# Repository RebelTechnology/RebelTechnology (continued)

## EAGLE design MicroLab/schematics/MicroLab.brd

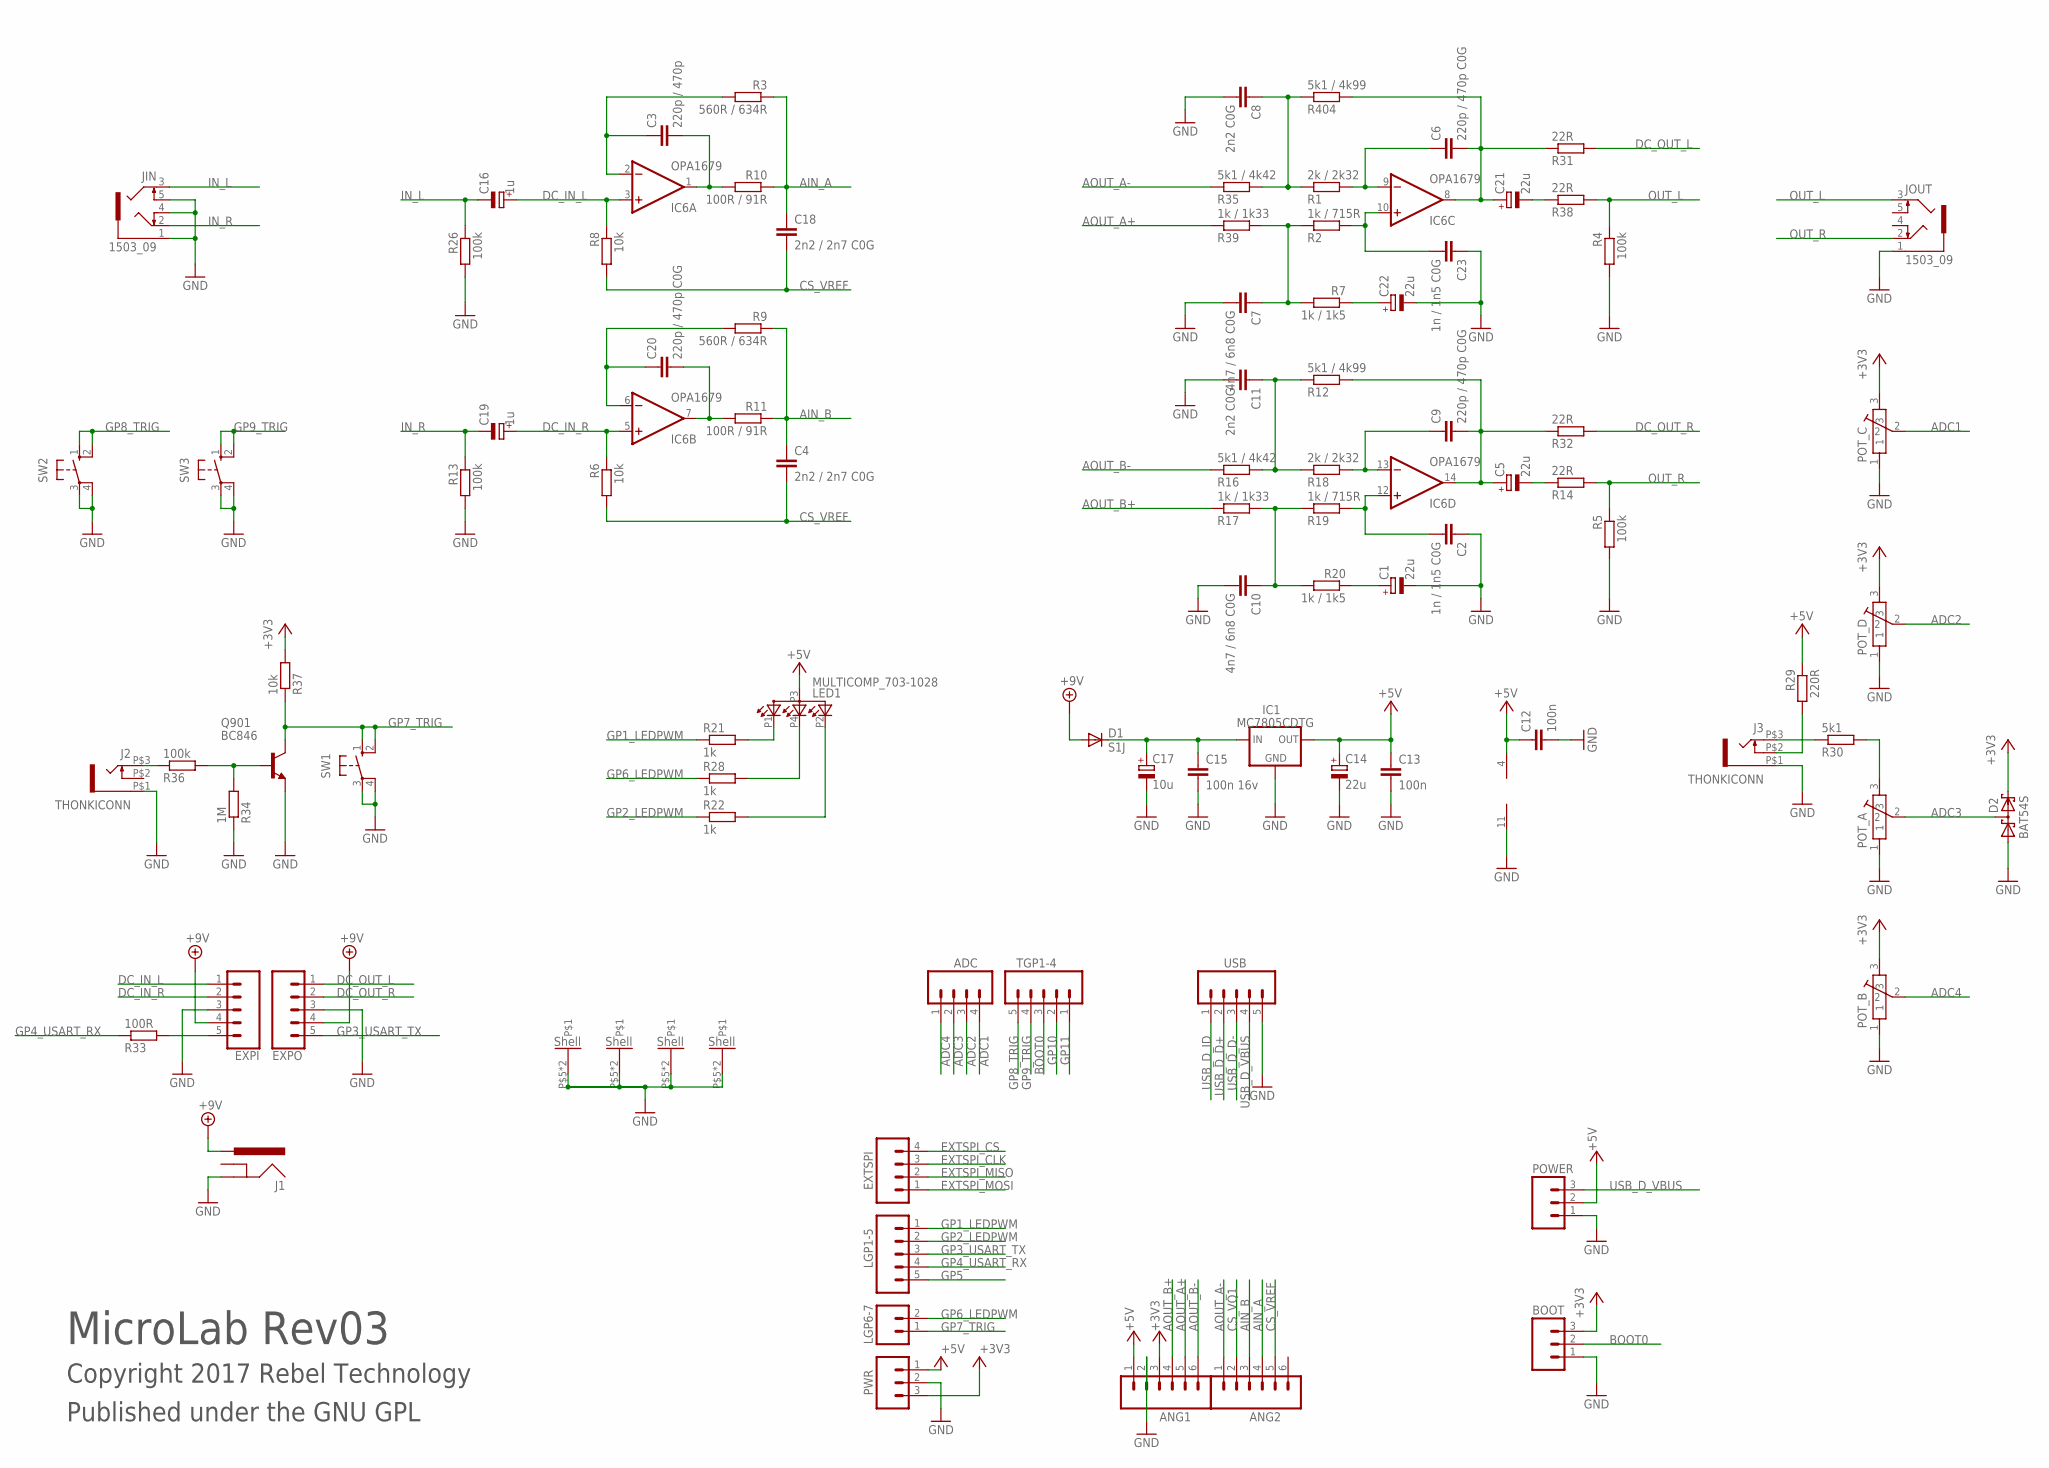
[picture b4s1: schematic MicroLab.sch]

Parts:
ADC: M04PTH; 1X04
ANG1, ANG2: M06SIP; 1X06
BOOT: M03PTH; 1X03
C1, C5, C14, C21, C22: 22u; CPOL-5
C2, C23: 1n / 1n5 C0G; C0603
C3: 220p / 470p; C0603
C4, C18: 2n2 / 2n7 C0G; C0603
C6, C9, C20: 220p / 470p C0G; C0603
C7, C10: 4n7 / 6n8 C0G; C0603
C8, C11: 2n2 C0G; C0603
C12, C13: 100n; C0603
C15: 100n 16v; C0603
C16, C19: 1u; 153CLV-0405
C17: 10u; 153CLV-0405
D1: S1J; SMA-DIODE
D2: BAT54S; SOT23
EXPI: CONN_05JST-VERT; JST-5-PTH-VERT
EXPO: CONN_05JST-VERT; JST-5-PTH-VERT
EXTSPI: M04PTH; 1X04
IC1: MC7805CDTG; DPACK
IC6: OPA1679; SO14
J1: POWER_JACKPTH; POWER_JACK_PTH
J2, J3: THONKICONN
JIN: 1503_09
JOUT: 1503_09
LED1: MULTICOMP_703-1028; RGB-LED-703-1028
LGP1-5: M05PTH; 1X05
LGP6-7: M02PTH; 1X02
POT_A: POT-ALPS-RK09L1140
POT_B: POT-ALPS-RK09L1140
POT_C: POT-ALPS-RK09L1140
POT_D: POT-ALPS-RK09L1140
POWER: M03PTH; 1X03
PWR: M03PTH; 1X03
Q901: BC846; SOT23
R1, R18: 2k / 2k32; 0603
R2, R19: 1k / 715R; 0603
R3, R9: 560R / 634R; 0603
R4, R5, R13, R26, R36: 100k; 0603
R6, R8, R37: 10k; 0603
R7, R20: 1k / 1k5; 0603
R10, R11: 100R / 91R; 0603
R12, R404: 5k1 / 4k99; 0603
R14, R31, R32, R38: 22R; 0603
R16, R35: 5k1 / 4k42; 0603
R17, R39: 1k / 1k33; 0603
R21, R22, R28: 1k; 0603
R29: 220R; 0603
R30: 5k1; 0603
R33: 100R; 0603
R34: 1M; 0603
SW1, SW2, SW3: 10-XX; B3F-10XX
TGP1-4: M05PTH; 1X05
USB: M05PTH; 1X05

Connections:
+3V3: ANG1.3, BOOT.3, D2.2 (C2), POT_B.3, POT_C.3, POT_D.3, PWR.3, R37.2
+5V: ANG1.1, C12.1, C13.1, C14.+, IC1.3 (OUT), IC6.4 (V+), LED1.P3 (A), POWER.2, PWR.1, R29.1
+9V: D1.A, EXPI.4, EXPO.4, J1.PWR
ADC1: ADC.4, POT_C.2
ADC2: ADC.3, POT_D.2
ADC3: ADC.2, D2.3 (C1A2), POT_A.2
ADC4: ADC.1, POT_B.2
AIN_A: ANG2.4, C18.1, R3.1, R10.1
AIN_B: ANG2.3, C4.1, R9.1, R11.1
AOUT_A+: ANG1.5, R39.1
AOUT_A-: ANG2.1, R35.1
AOUT_B+: ANG1.4, R17.1
AOUT_B-: ANG1.6, R16.1
BOOT0: BOOT.2, TGP1-4.3
CS_VQ1: ANG2.2
CS_VREF: ANG2.5, C4.2, C18.2, R6.2, R8.2
DC_IN_L: C16.+, EXPI.1, IC6.3 (+IN), R8.1
DC_IN_R: C19.+, EXPI.2, IC6.5 (+IN), R6.1
DC_OUT_L: EXPO.1, R31.2
DC_OUT_R: EXPO.2, R32.2
EXTSPI_CLK: EXTSPI.3
EXTSPI_CS: EXTSPI.4
EXTSPI_MISO: EXTSPI.2
EXTSPI_MOSI: EXTSPI.1
GND: ANG1.2, BOOT.1, C1.-, C2.1, C7.2, C8.2, C10.2, C11.2, C12.2, C13.2, C14.-, C15.2, C17.-, C22.-, C23.1, D2.1 (A1), EXPI.3, EXPO.3, IC1.4 (GND), IC6.11 (V-), J1.GND, J2.P$1 (5), J3.P$1 (5), JIN.1, JIN.4, JIN.5, JOUT.1, POT_A.1, POT_A.P$5, POT_A.P$6, POT_B.1, POT_B.P$5, POT_B.P$6, POT_C.1, POT_C.P$5, POT_C.P$6, POT_D.1, POT_D.P$5, POT_D.P$6, POWER.1, PWR.2, Q901.2 (E), R4.2, R5.2, R13.2, R26.2, R34.1, SW1.3, SW1.4 (P1), SW2.3, SW2.4 (P1), SW3.3, SW3.4 (P1), USB.5
GP1_LEDPWM: LGP1-5.1, R21.1
GP2_LEDPWM: LGP1-5.2, R22.1
GP3_USART_TX: EXPO.5, LGP1-5.3
GP4_USART_RX: LGP1-5.4, R33.1
GP5: LGP1-5.5
GP6_LEDPWM: LGP6-7.2, R28.1
GP7_TRIG: LGP6-7.1, Q901.3 (C), R37.1, SW1.1 (S), SW1.2 (S1)
GP8_TRIG: SW2.1 (S), SW2.2 (S1), TGP1-4.5
GP9_TRIG: SW3.1 (S), SW3.2 (S1), TGP1-4.4
GP10: TGP1-4.2
GP11: TGP1-4.1
IN_L: C16.-, JIN.3, R26.1
IN_R: C19.-, JIN.2, R13.1
unnamed: EXPI.5, R33.2
unnamed: C3.1, IC6.2 (-IN), R3.2
unnamed: C20.2, IC6.7 (OUT), R11.2
unnamed: C20.1, IC6.6 (-IN), R9.2
unnamed: C3.2, IC6.1 (OUT), R10.2
unnamed: C6.1, IC6.9 (-IN), R1.2
unnamed: C1.+, R20.1
unnamed: C21.-, R38.1
unnamed: C22.+, R7.1
unnamed: C23.2, IC6.10 (+IN), R2.2
unnamed: C5.+, C9.2, IC6.14 (OUT), R12.2, R32.1
unnamed: C5.-, R14.1
unnamed: C7.1, R2.1, R7.2, R39.2
unnamed: LED1.P1 (CRED), R21.2
unnamed: LED1.P2 (CGREEN), R22.2
unnamed: LED1.P4 (CBLUE), R28.2
unnamed: J2.P$3 (3), R36.1
unnamed: J3.P$2 (4), R29.2
unnamed: C11.1, R12.1, R16.2, R18.1
unnamed: POT_A.3, R30.2
unnamed: C9.1, IC6.13 (-IN), R18.2
unnamed: J3.P$3 (3), R30.1
unnamed: C15.1, C17.+, D1.C, IC1.1 (IN)
unnamed: C2.2, IC6.12 (+IN), R19.2
unnamed: C10.1, R17.2, R19.1, R20.2
unnamed: Q901.1 (B), R34.2, R36.2
unnamed: C6.2, C21.+, IC6.8 (OUT), R31.1, R404.2
unnamed: C8.1, R1.1, R35.2, R404.1
OUT_L: JOUT.3, R4.1, R38.2
OUT_R: JOUT.2, R5.1, R14.2
USB_D_D+: USB.2
USB_D_D-: USB.3
USB_D_ID: USB.1
USB_D_VBUS: POWER.3, USB.4

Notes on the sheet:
MicroLab Rev03
Copyright 2017 Rebel Technology
Published under the GNU GPL

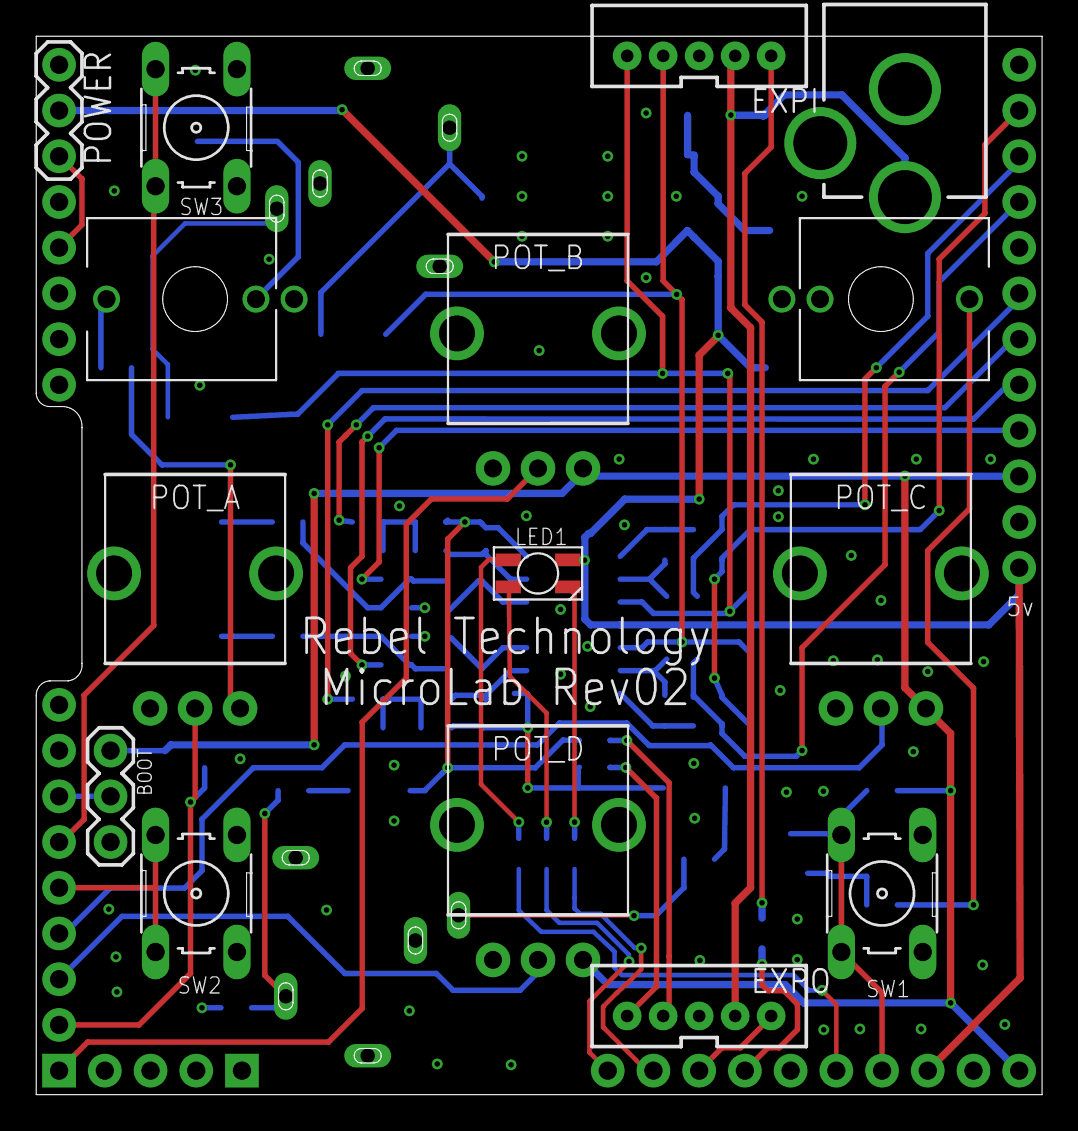
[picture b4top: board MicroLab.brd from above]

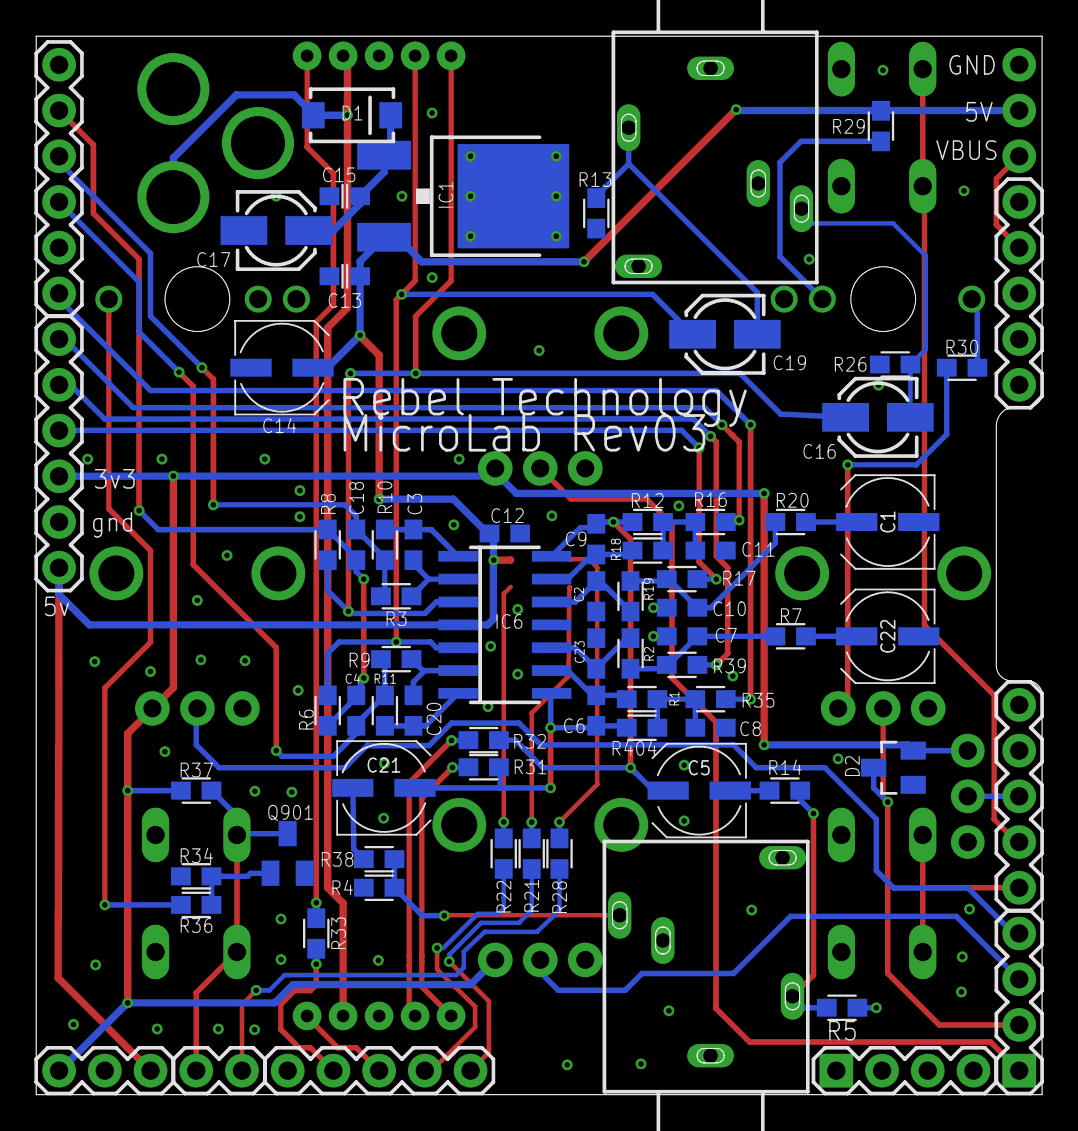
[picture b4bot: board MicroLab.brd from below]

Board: 2 copper layers, 55.9 x 58.8 mm, 89 parts (74 on the bottom side), 61 nets.

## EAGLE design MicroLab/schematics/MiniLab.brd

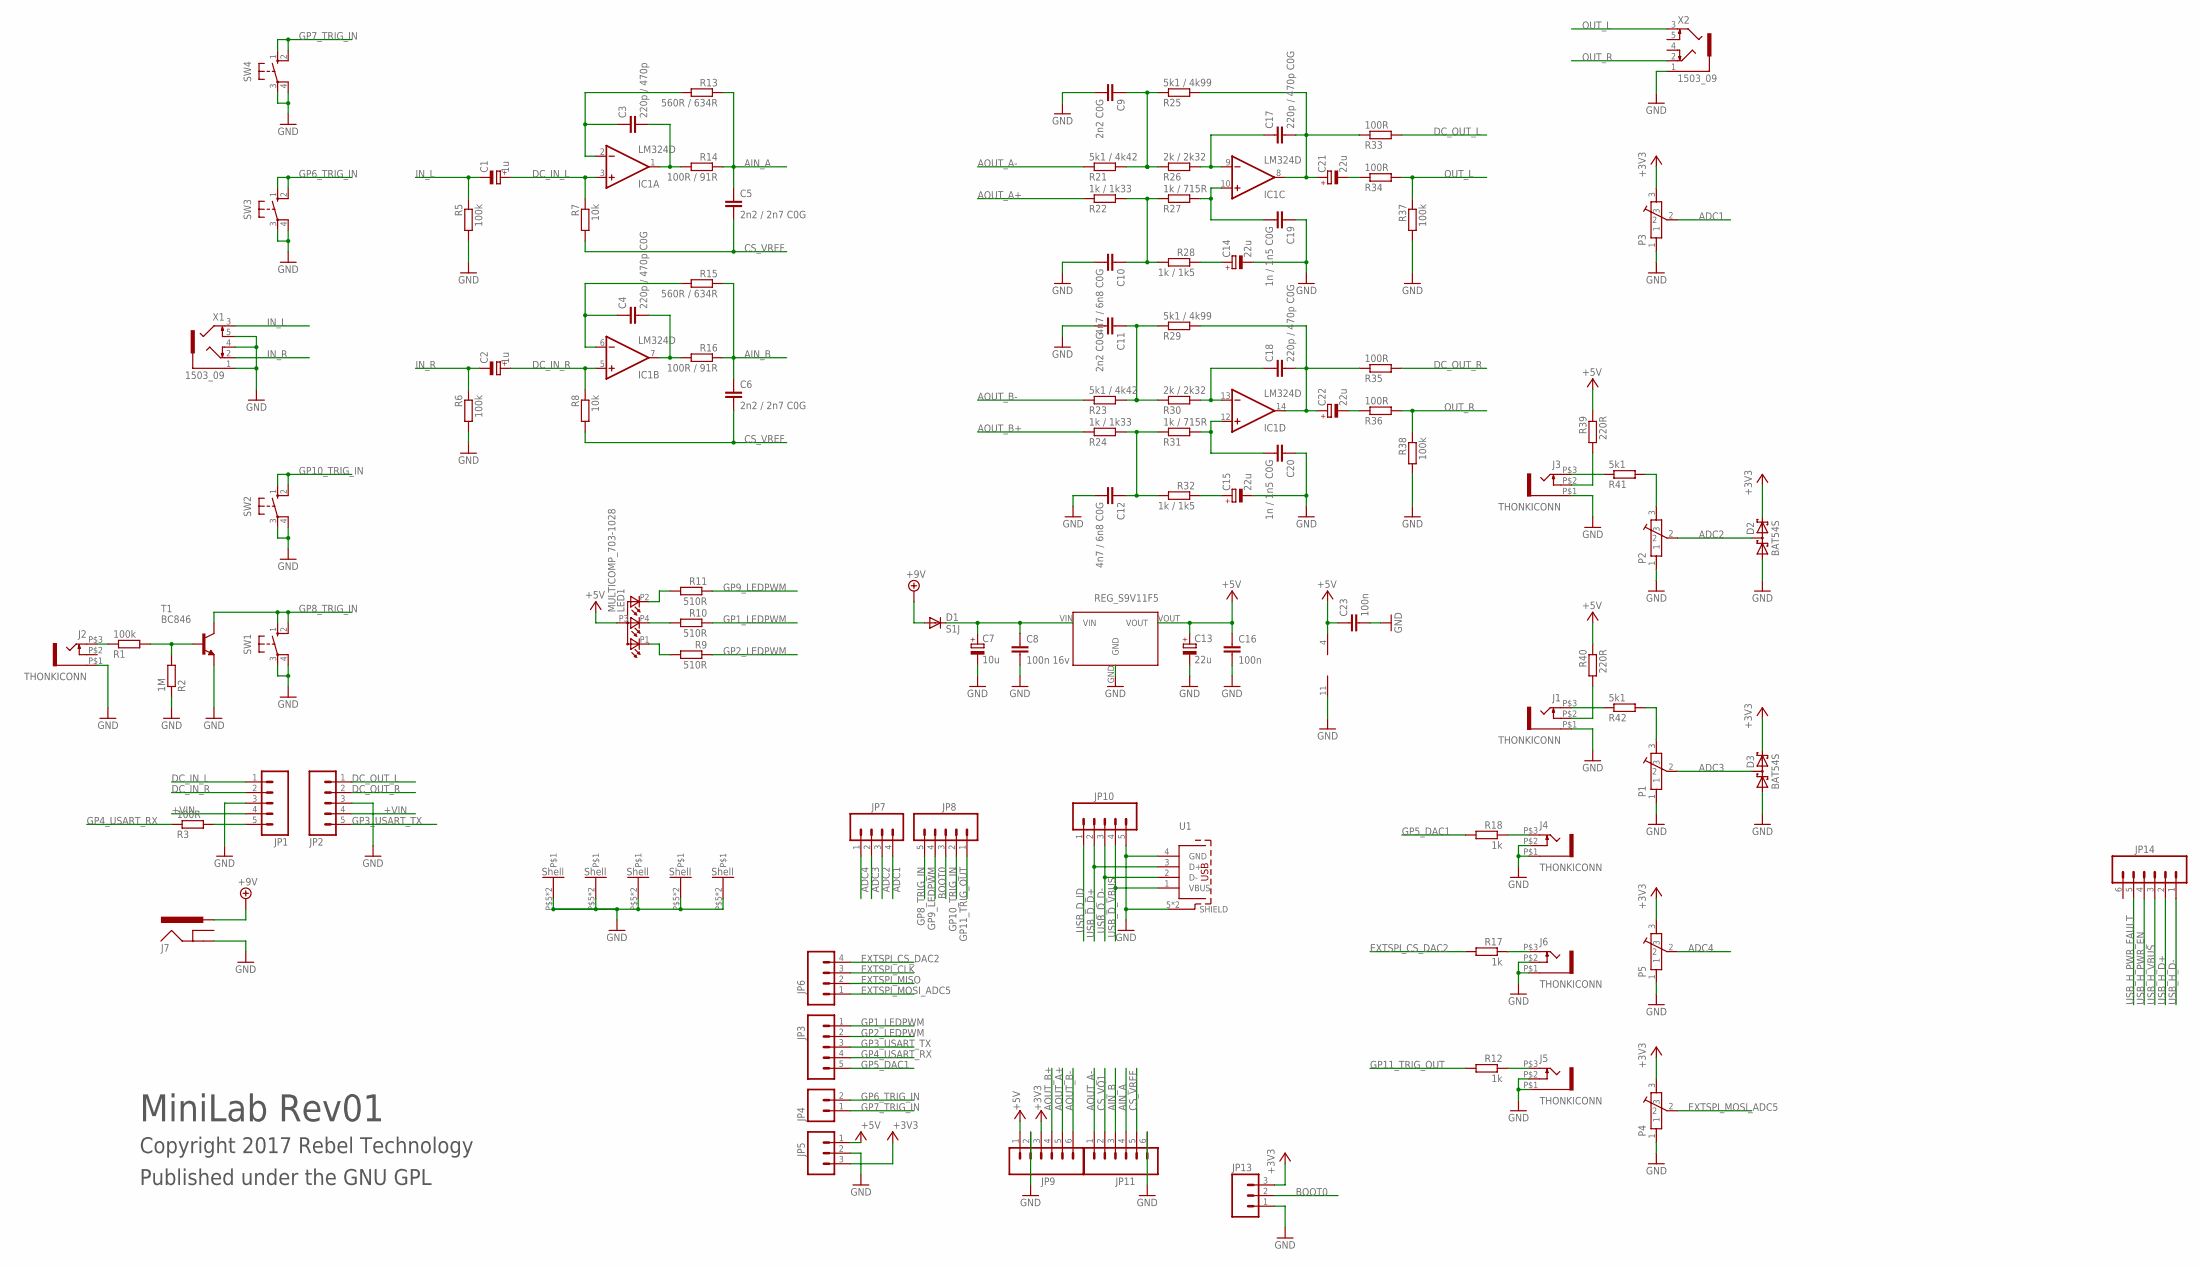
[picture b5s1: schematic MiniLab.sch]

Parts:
C1, C2: 1u; 153CLV-0405
C3: 220p / 470p; C0603
C4, C17, C18: 220p / 470p C0G; C0603
C5, C6: 2n2 / 2n7 C0G; C0603
C7: 10u; 153CLV-0405
C8: 100n 16v; C0603
C9, C11: 2n2 C0G; C0603
C10, C12: 4n7 / 6n8 C0G; C0603
C13, C14, C15, C21, C22: 22u; CPOL-5
C16, C23: 100n; C0603
C19, C20: 1n / 1n5 C0G; C0603
D1: S1J; SMA-DIODE
D2, D3: BAT54S; SOT23
IC1: LM324D; SO14
J1, J2, J3, J4, J5, J6: THONKICONN
J7: POWER_JACKPTH; POWER_JACK_PTH
JP1, JP2, JP3, JP8, JP10: M05PTH; 1X05
JP4: M02PTH; 1X02
JP5, JP13: M03PTH; 1X03
JP6, JP7: M04PTH; 1X04
JP9, JP11, JP14: M06SIP; 1X06
LED1: MULTICOMP_703-1028; RGB-LED-703-1028
P1, P2, P3, P4, P5: POT-ALPS-RK09L1140
R1, R5, R6, R37, R38: 100k; 0603
R2: 1M; 0603
R3, R33, R34, R35, R36: 100R; 0603
R7, R8: 10k; 0603
R9, R10, R11: 510R; 0603
R12, R17, R18: 1k; 0603
R13, R15: 560R / 634R; 0603
R14, R16: 100R / 91R; 0603
R21, R23: 5k1 / 4k42; 0603
R22, R24: 1k / 1k33; 0603
R25, R29: 5k1 / 4k99; 0603
R26, R30: 2k / 2k32; 0603
R27, R31: 1k / 715R; 0603
R28, R32: 1k / 1k5; 0603
R39, R40: 220R; 0603
R41, R42: 5k1; 0603
SW1, SW2, SW3, SW4: 10-XX; B3F-10XX
T1: BC846; SOT23
U1: 614104190121
U2: REG_S9V11F5
X1, X2: 1503_09

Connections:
+3V3: D2.2 (C2), D3.2 (C2), JP5.3, JP9.3, JP13.3, P3.3, P4.3, P5.3
+5V: C13.+, C16.1, C23.1, IC1.4 (V+), JP5.1, JP9.1, LED1.P3 (A), R39.1, R40.1, U2.VOUT; also elsewhere on the board
+9V: D1.A, J7.PWR
+VIN: C7.+, C8.1, D1.C, JP1.4, JP2.4, U2.VIN
ADC1: JP7.4, P3.2
ADC2: D2.3 (C1A2), JP7.3, P2.2
ADC3: D3.3 (C1A2), JP7.2, P1.2
ADC4: JP7.1, P5.2
AIN_A: C5.1, JP11.4, R13.1, R14.1
AIN_B: C6.1, JP11.3, R15.1, R16.1
AOUT_A+: JP9.5, R22.1
AOUT_A-: JP11.1, R21.1
AOUT_B+: JP9.4, R24.1
AOUT_B-: JP9.6, R23.1
BOOT0: JP8.3, JP13.2
CS_VQ1: JP11.2
CS_VREF: C5.2, C6.2, JP11.5, R7.2, R8.2
DC_IN_L: C1.+, IC1.3 (+IN), JP1.1, R7.1
DC_IN_R: C2.+, IC1.5 (+IN), JP1.2, R8.1
DC_OUT_L: JP2.1, R33.2
DC_OUT_R: JP2.2, R35.2
EXTSPI_CLK: JP6.3
EXTSPI_CS_DAC2: JP6.4, R17.2
EXTSPI_MISO: JP6.2
EXTSPI_MOSI_ADC5: JP6.1, P4.2
GND: C7.-, C8.2, C9.2, C10.2, C11.2, C12.2, C13.-, C14.-, C15.-, C16.2, C19.1, C20.1, C23.2, D2.1 (A1), D3.1 (A1), IC1.11 (V-), J1.P$1 (5), J2.P$1 (5), J3.P$1 (5), J4.P$1 (5), J4.P$2 (4), J5.P$1 (5), J5.P$2 (4), J6.P$1 (5), J6.P$2 (4), J7.GND, JP1.3, JP2.3, JP5.2, JP9.2, JP10.5, JP11.6, JP13.1, P1.1, P1.P$5, P1.P$6, P2.1, P2.P$5, P2.P$6, P3.1, P3.P$5, P3.P$6, P4.1, P4.P$5, P4.P$6, P5.1, P5.P$5, P5.P$6, R2.1, R5.2, R6.2, R37.2, R38.2, SW1.3, SW1.4 (P1), SW2.3, SW2.4 (P1), SW3.3, SW3.4 (P1), SW4.3, SW4.4 (P1), T1.2 (E), U1.4 (GND), U1.5 (SHIELD), U1.6 (SHIELD), U2.GND, X1.1, X1.4, X1.5, X2.1; also elsewhere on the board
GP1_LEDPWM: JP3.1, R10.1
GP2_LEDPWM: JP3.2, R9.1
GP3_USART_TX: JP2.5, JP3.3
GP4_USART_RX: JP3.4, R3.1
GP5_DAC1: JP3.5, R18.2
GP6_TRIG_IN: JP4.2, SW3.1 (S), SW3.2 (S1)
GP7_TRIG_IN: JP4.1, SW4.1 (S), SW4.2 (S1)
GP8_TRIG_IN: JP8.5, SW1.1 (S), SW1.2 (S1), T1.3 (C)
GP9_LEDPWM: JP8.4, R11.1
GP10_TRIG_IN: JP8.2, SW2.1 (S), SW2.2 (S1)
GP11_TRIG_OUT: JP8.1, R12.2
IN_L: C1.-, R5.1, X1.3
IN_R: C2.-, R6.1, X1.2
unnamed: JP1.5, R3.2
unnamed: J1.P$2 (4), R40.2
unnamed: C3.1, IC1.2 (-IN), R13.2
unnamed: C4.2, IC1.7 (OUT), R16.2
unnamed: C4.1, IC1.6 (-IN), R15.2
unnamed: C3.2, IC1.1 (OUT), R14.2
unnamed: C17.1, IC1.9 (-IN), R26.2
unnamed: C15.+, R32.1
unnamed: C21.-, R34.1
unnamed: C14.+, R28.1
unnamed: C19.2, IC1.10 (+IN), R27.2
unnamed: C18.2, C22.+, IC1.14 (OUT), R29.2, R35.1
unnamed: C22.-, R36.1
unnamed: LED1.P2 (CGREEN), R11.2
unnamed: C10.1, R22.2, R27.1, R28.2
unnamed: LED1.P1 (CRED), R9.2
unnamed: LED1.P4 (CBLUE), R10.2
unnamed: J5.P$3 (3), R12.1
unnamed: J6.P$3 (3), R17.1
unnamed: J4.P$3 (3), R18.1
unnamed: J2.P$3 (3), R1.1
unnamed: J3.P$2 (4), R39.2
unnamed: C11.1, R23.2, R29.1, R30.1
unnamed: P2.3, R41.2
unnamed: C18.1, IC1.13 (-IN), R30.2
unnamed: J3.P$3 (3), R41.1
unnamed: C20.2, IC1.12 (+IN), R31.2
unnamed: P1.3, R42.2
unnamed: C12.1, R24.2, R31.1, R32.2
unnamed: J1.P$3 (3), R42.1
unnamed: R1.2, R2.2, T1.1 (B)
unnamed: C17.2, C21.+, IC1.8 (OUT), R25.2, R33.1
unnamed: C9.1, R21.2, R25.1, R26.1
OUT_L: R34.2, R37.1, X2.3
OUT_R: R36.2, R38.1, X2.2
USB_D_ID: JP10.1
USB_H_PWR_EN: JP14.4; also elsewhere on the board
USB_H_PWR_FAULT: JP14.5; also elsewhere on the board

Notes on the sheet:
MiniLab Rev01
Copyright 2017 Rebel Technology
Published under the GNU GPL

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
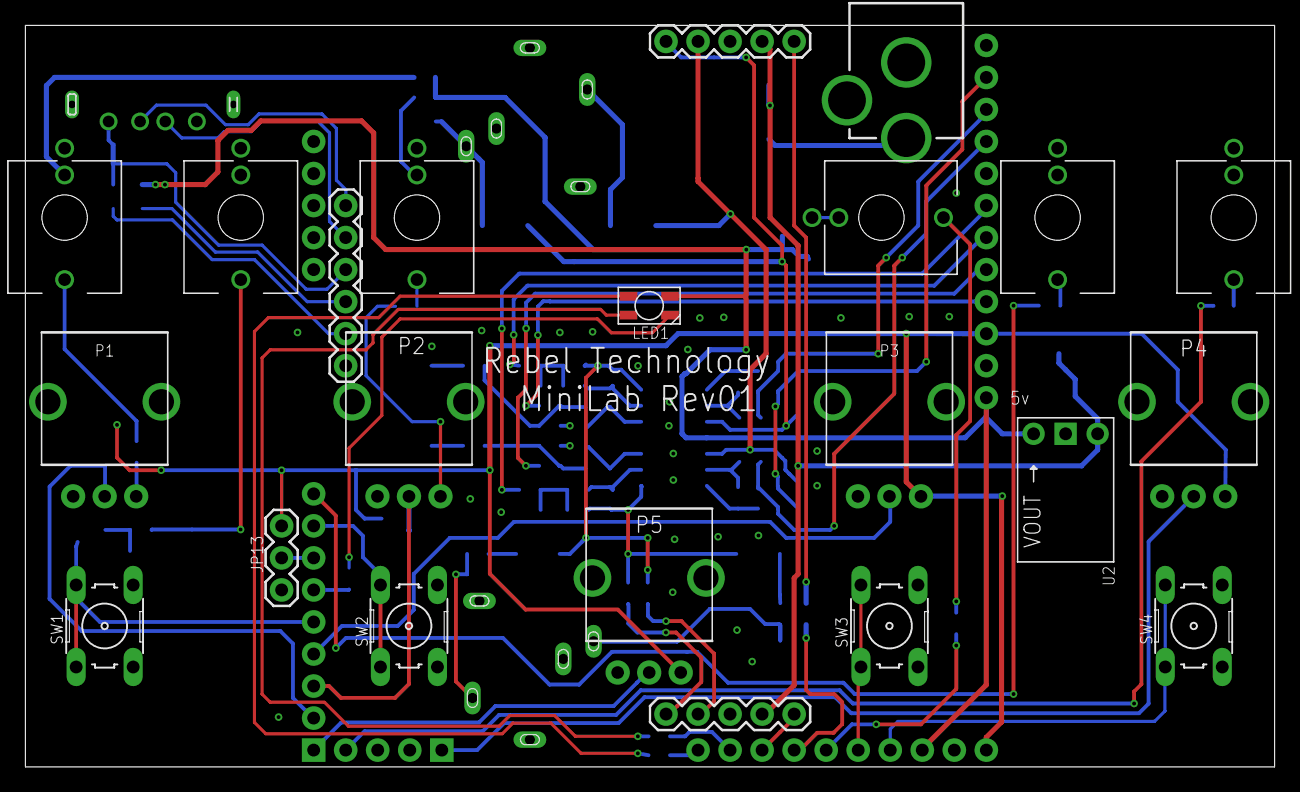
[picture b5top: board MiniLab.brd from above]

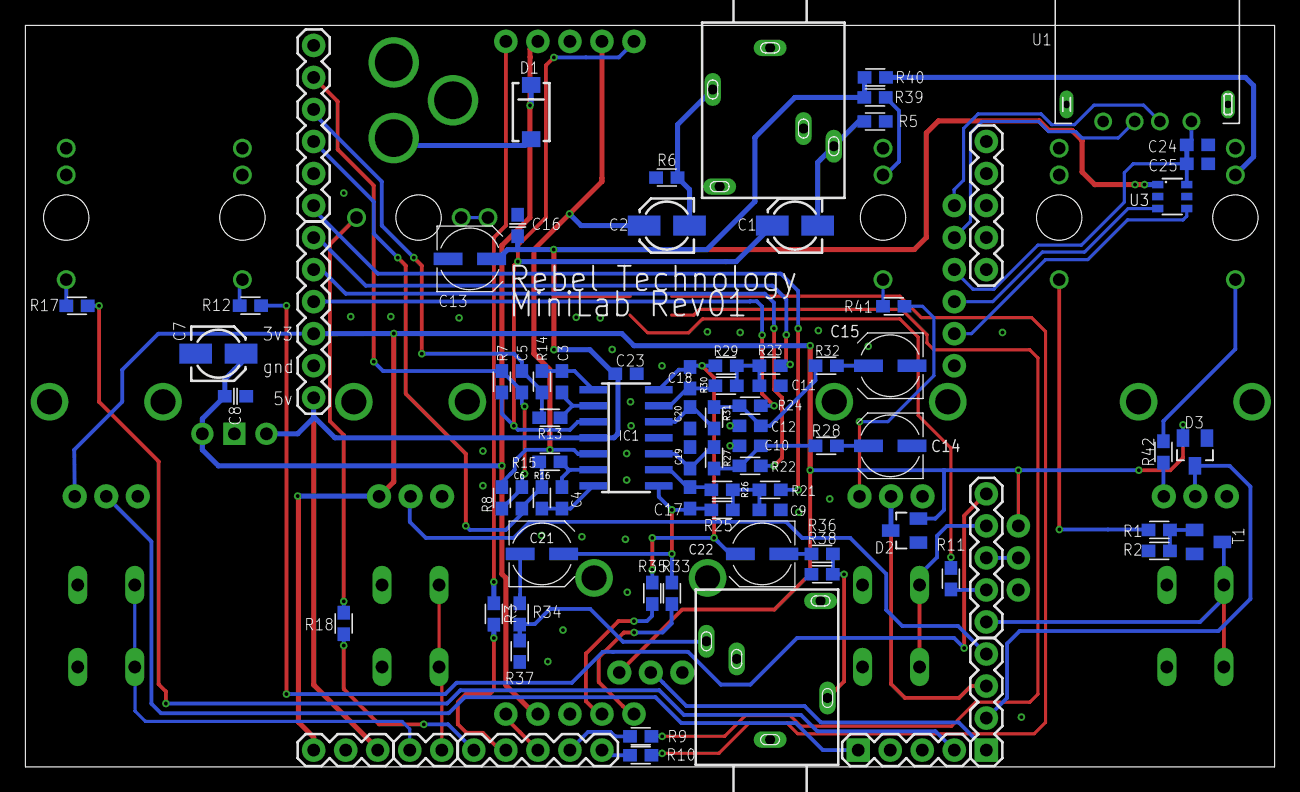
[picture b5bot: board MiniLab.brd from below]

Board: 2 copper layers, 99.1 x 58.8 mm, 104 parts (82 on the bottom side), 76 nets.

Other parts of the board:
C24, C25: 10u; C0603
U3: MIC2005; SOT23-6

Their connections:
+5V: U3.1; also elsewhere on the board
GND: C24.1, C25.1; also elsewhere on the board
USB_H_PWR_EN: U3.3; also elsewhere on the board
USB_H_PWR_FAULT: U3.4; also elsewhere on the board

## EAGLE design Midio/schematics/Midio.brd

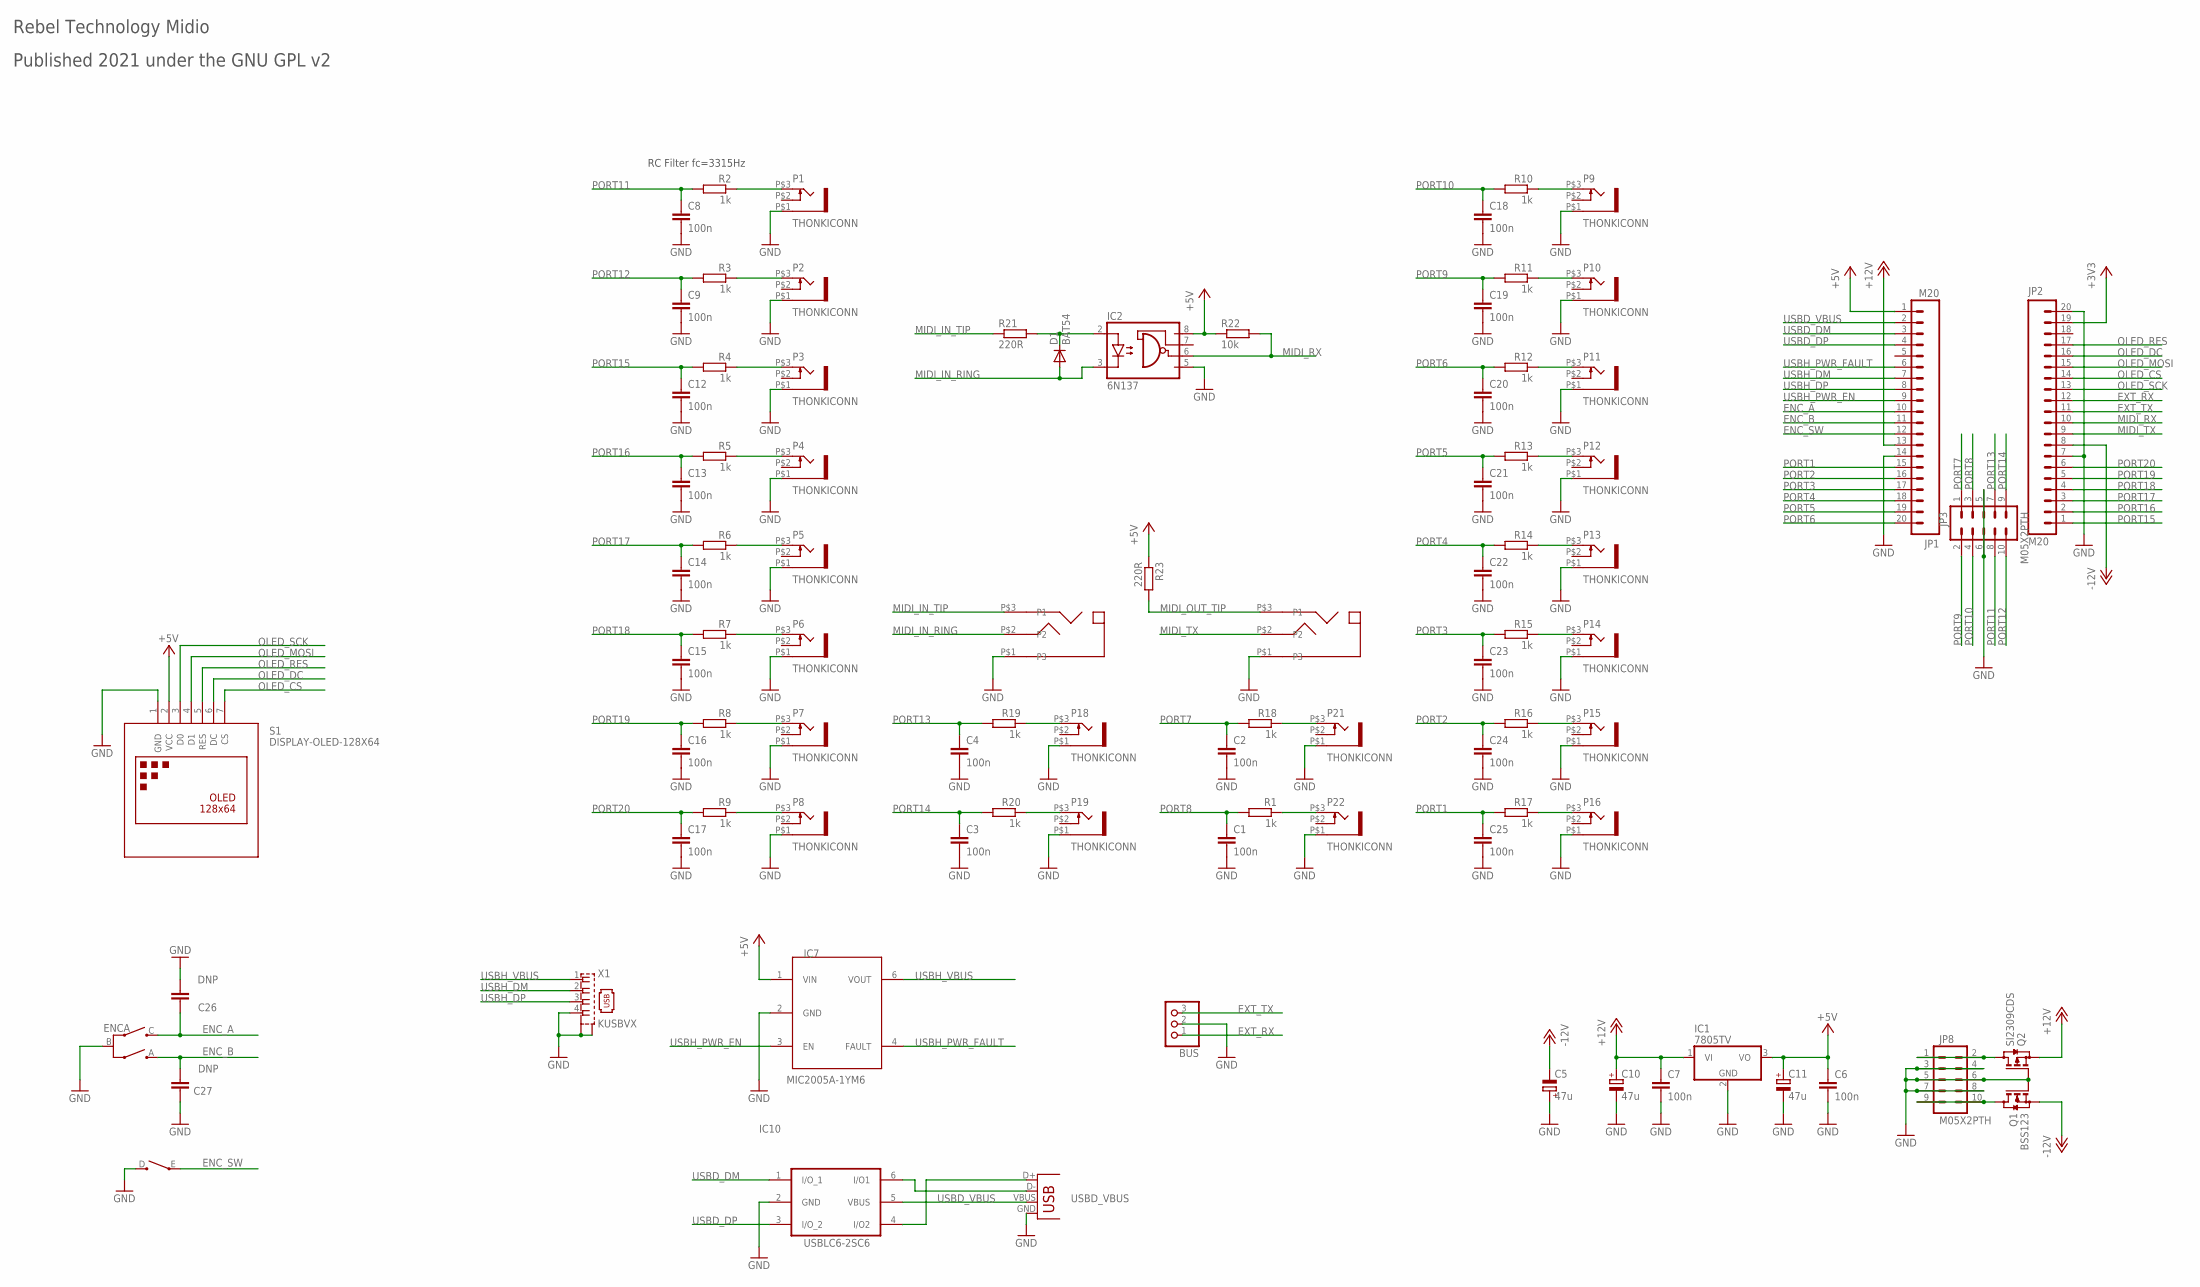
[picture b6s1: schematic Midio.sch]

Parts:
BUS: CON-JST-1X03PH-TH; JST-B3B-PH-KL
C1, C2, C3, C4, C6, C7, C8, C9, C12, C13, C14, C15, C16, C17, C18, C19, C20, C21, C22, C23, C24, C25: 100n; C0603
C5, C10, C11: 47u; UD-4X5,8_NICHICON
C26, C27: DNP; C0603
D1: BAT54; SOT23-R
ENC: CI-11
IC1: 7805TV; TO220V
IC2: 6N137; DIL08
IC7: MIC2005A-1YM6; SOT23-6
IC10: USBLC6-2SC6; SOT-23-6L
J1, J2: THONKICONN_STEREO
JP1, JP2: M20; 1X20
JP3, JP8: M05X2PTH; AVR_ICSP
P1, P2, P3, P4, P5, P6, P7, P8, P9, P10, P11, P12, P13, P14, P15, P16, P18, P19, P21, P22: THONKICONN
Q1: BSS123; SOT23
Q2: SI2309CDS; SOT23
R1, R2, R3, R4, R5, R6, R7, R8, R9, R10, R11, R12, R13, R14, R15, R16, R17, R18, R19, R20: 1k; 0603
R21, R23: 220R; 0603
R22: 10k; 0603
S1: DISPLAY-OLED-128X64
X1: KUSBVX
X2: USBPTH-VERTICAL; USB-B-PTH-VERTICAL

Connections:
+3V3: JP2.19
+5V: C6.1, C11.+, IC1.3 (VO), IC2.8 (VCC), IC7.1 (VIN), JP1.1, R22.1, R23.1, S1.2 (VCC)
+12V: C7.1, C10.+, IC1.1 (VI), JP1.13, Q2.2 (S)
-12V: C5.-, JP2.8, Q1.2 (S)
ENC_A: C26.1, ENC.C (B), JP1.10
ENC_B: C27.1, ENC.A, JP1.11
ENC_SW: ENC.E, JP1.12
EXT_RX: BUS.1, JP2.12
EXT_TX: BUS.3, JP2.11
GND: BUS.2, C1.2, C2.2, C3.2, C4.2, C5.+, C6.2, C7.2, C8.2, C9.2, C10.-, C11.-, C12.2, C13.2, C14.2, C15.2, C16.2, C17.2, C18.2, C19.2, C20.2, C21.2, C22.2, C23.2, C24.2, C25.2, C26.2, C27.2, ENC.B (C), ENC.D, IC1.2 (GND), IC2.5 (GND), IC7.2 (GND), IC10.2 (GND), J1.P$1 (P3), J2.P$1 (P3), JP1.14, JP2.7, JP2.20, JP3.5, JP3.6, JP8.3, JP8.4, JP8.5, JP8.6, JP8.7, JP8.8, P1.P$1 (5), P2.P$1 (5), P3.P$1 (5), P4.P$1 (5), P5.P$1 (5), P6.P$1 (5), P7.P$1 (5), P8.P$1 (5), P9.P$1 (5), P10.P$1 (5), P11.P$1 (5), P12.P$1 (5), P13.P$1 (5), P14.P$1 (5), P15.P$1 (5), P16.P$1 (5), P18.P$1 (5), P19.P$1 (5), P21.P$1 (5), P22.P$1 (5), Q1.1 (G), Q2.1 (G), S1.1 (GND), X1.4, X1.M1 (S1), X1.M2 (S2), X2.GND
MIDI_IN_RING: D1.1 (A), IC2.3 (C), J1.P$2 (P2)
MIDI_IN_TIP: J1.P$3 (P1), R21.1
MIDI_OUT_TIP: J2.P$3 (P1), R23.2
MIDI_RX: IC2.6 (VO), JP2.10, R22.2
MIDI_TX: J2.P$2 (P2), JP2.9
unnamed: P8.P$3 (3), R9.1
unnamed: P7.P$3 (3), R8.1
unnamed: P6.P$3 (3), R7.1
unnamed: P5.P$3 (3), R6.1
unnamed: P4.P$3 (3), R5.1
unnamed: P3.P$3 (3), R4.1
unnamed: P2.P$3 (3), R3.1
unnamed: P1.P$3 (3), R2.1
unnamed: P16.P$3 (3), R17.1
unnamed: P15.P$3 (3), R16.1
unnamed: P14.P$3 (3), R15.1
unnamed: P13.P$3 (3), R14.1
unnamed: P12.P$3 (3), R13.1
unnamed: P9.P$3 (3), R10.1
unnamed: P10.P$3 (3), R11.1
unnamed: P11.P$3 (3), R12.1
unnamed: P22.P$3 (3), R1.1
unnamed: P21.P$3 (3), R18.1
unnamed: P18.P$3 (3), R19.1
unnamed: P19.P$3 (3), R20.1
unnamed: D1.3 (C), IC2.2 (A), R21.2
unnamed: IC10.6 (I/O1), X2.D-
unnamed: IC10.4 (I/O2), X2.D+
unnamed: JP8.9, JP8.10, Q1.3 (D)
unnamed: JP8.1, JP8.2, Q2.3 (D)
OLED_CS: JP2.14, S1.7 (CS)
OLED_DC: JP2.16, S1.6 (DC)
OLED_MOSI: JP2.15, S1.4 (D1)
OLED_RES: JP2.17, S1.5 (RES)
OLED_SCK: JP2.13, S1.3 (D0)
PORT1: C25.1, JP1.15, R17.2
PORT2: C24.1, JP1.16, R16.2
PORT3: C23.1, JP1.17, R15.2
PORT4: C22.1, JP1.18, R14.2
PORT5: C21.1, JP1.19, R13.2
PORT6: C20.1, JP1.20, R12.2
PORT7: C2.1, JP3.1, R18.2
PORT8: C1.1, JP3.3, R1.2
PORT9: C19.1, JP3.2, R11.2
PORT10: C18.1, JP3.4, R10.2
PORT11: C8.1, JP3.8, R2.2
PORT12: C9.1, JP3.10, R3.2
PORT13: C4.1, JP3.7, R19.2
PORT14: C3.1, JP3.9, R20.2
PORT15: C12.1, JP2.1, R4.2
PORT16: C13.1, JP2.2, R5.2
PORT17: C14.1, JP2.3, R6.2
PORT18: C15.1, JP2.4, R7.2
PORT19: C16.1, JP2.5, R8.2
PORT20: C17.1, JP2.6, R9.2
USBD_DM: IC10.1 (I/O_1), JP1.3
USBD_DP: IC10.3 (I/O_2), JP1.4
USBD_VBUS: IC10.5 (VBUS), JP1.2, X2.VBUS
USBH_DM: JP1.7, X1.2
USBH_DP: JP1.8, X1.3
USBH_PWR_EN: IC7.3 (EN), JP1.9
USBH_PWR_FAULT: IC7.4 (FAULT), JP1.6
USBH_VBUS: IC7.6 (VOUT), X1.1

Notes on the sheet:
Rebel Technology Midio
Published 2021 under the GNU GPL v2
RC Filter fc=3315Hz

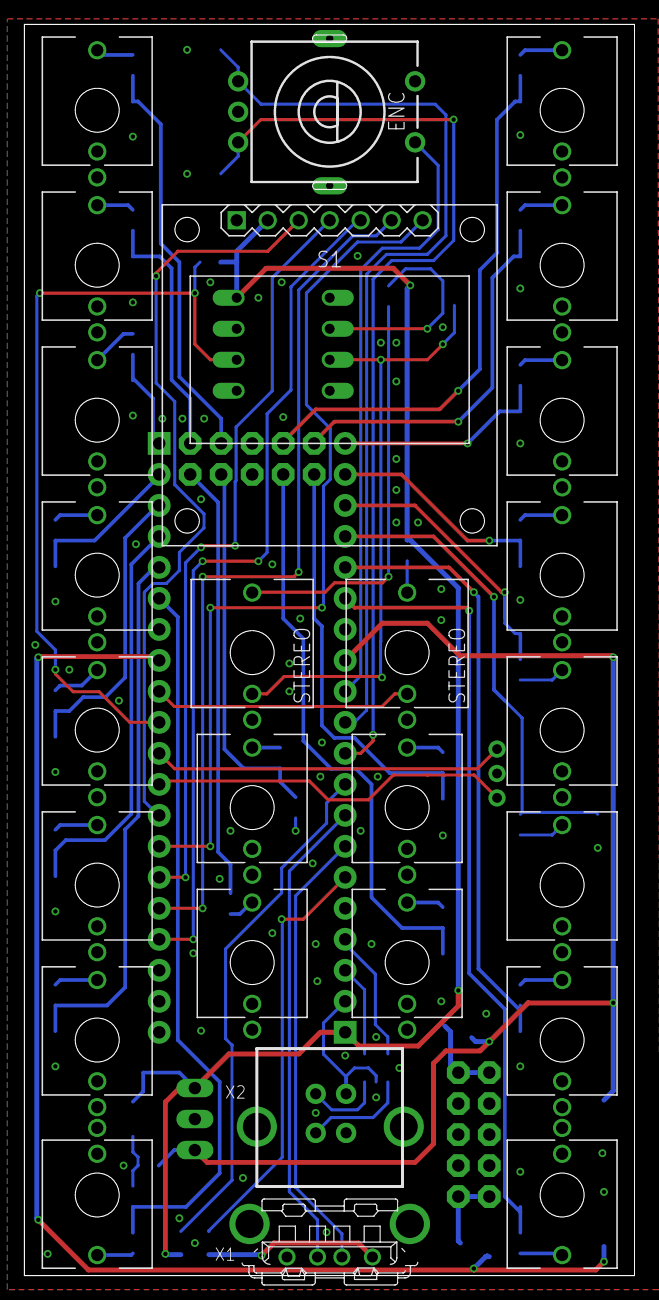
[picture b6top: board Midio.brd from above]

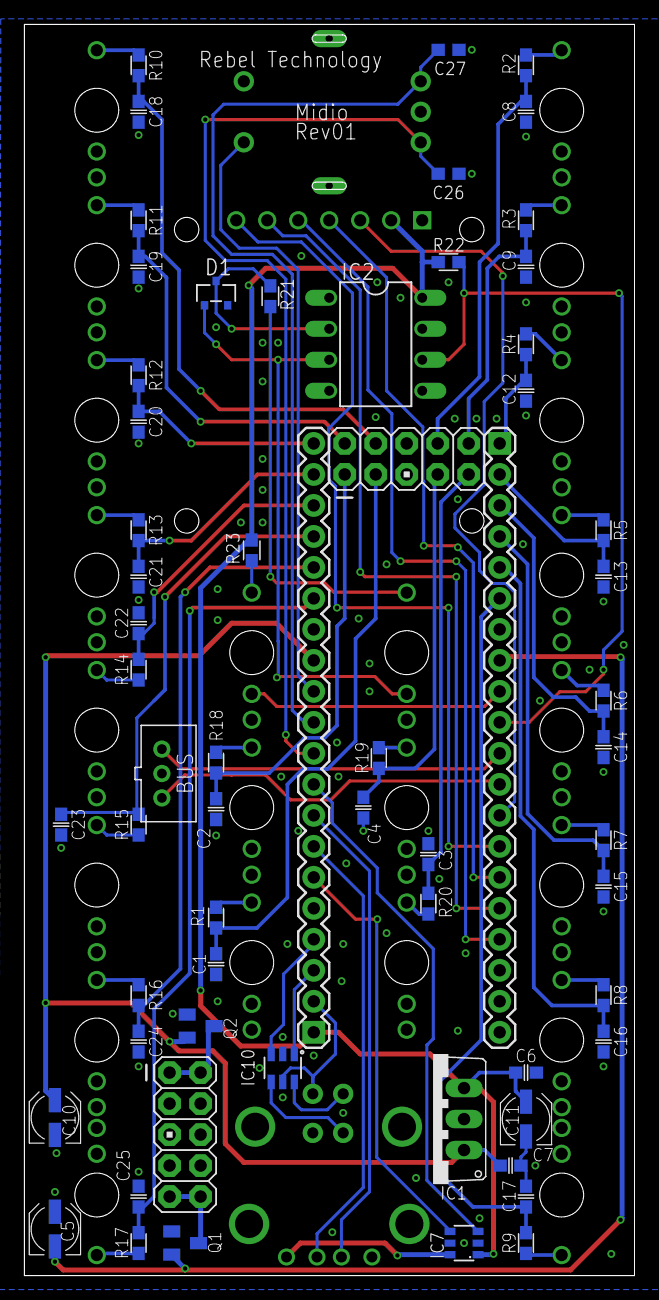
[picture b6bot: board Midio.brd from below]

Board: 2 copper layers, 50.0 x 102.5 mm, 88 parts (62 on the bottom side), 72 nets.
